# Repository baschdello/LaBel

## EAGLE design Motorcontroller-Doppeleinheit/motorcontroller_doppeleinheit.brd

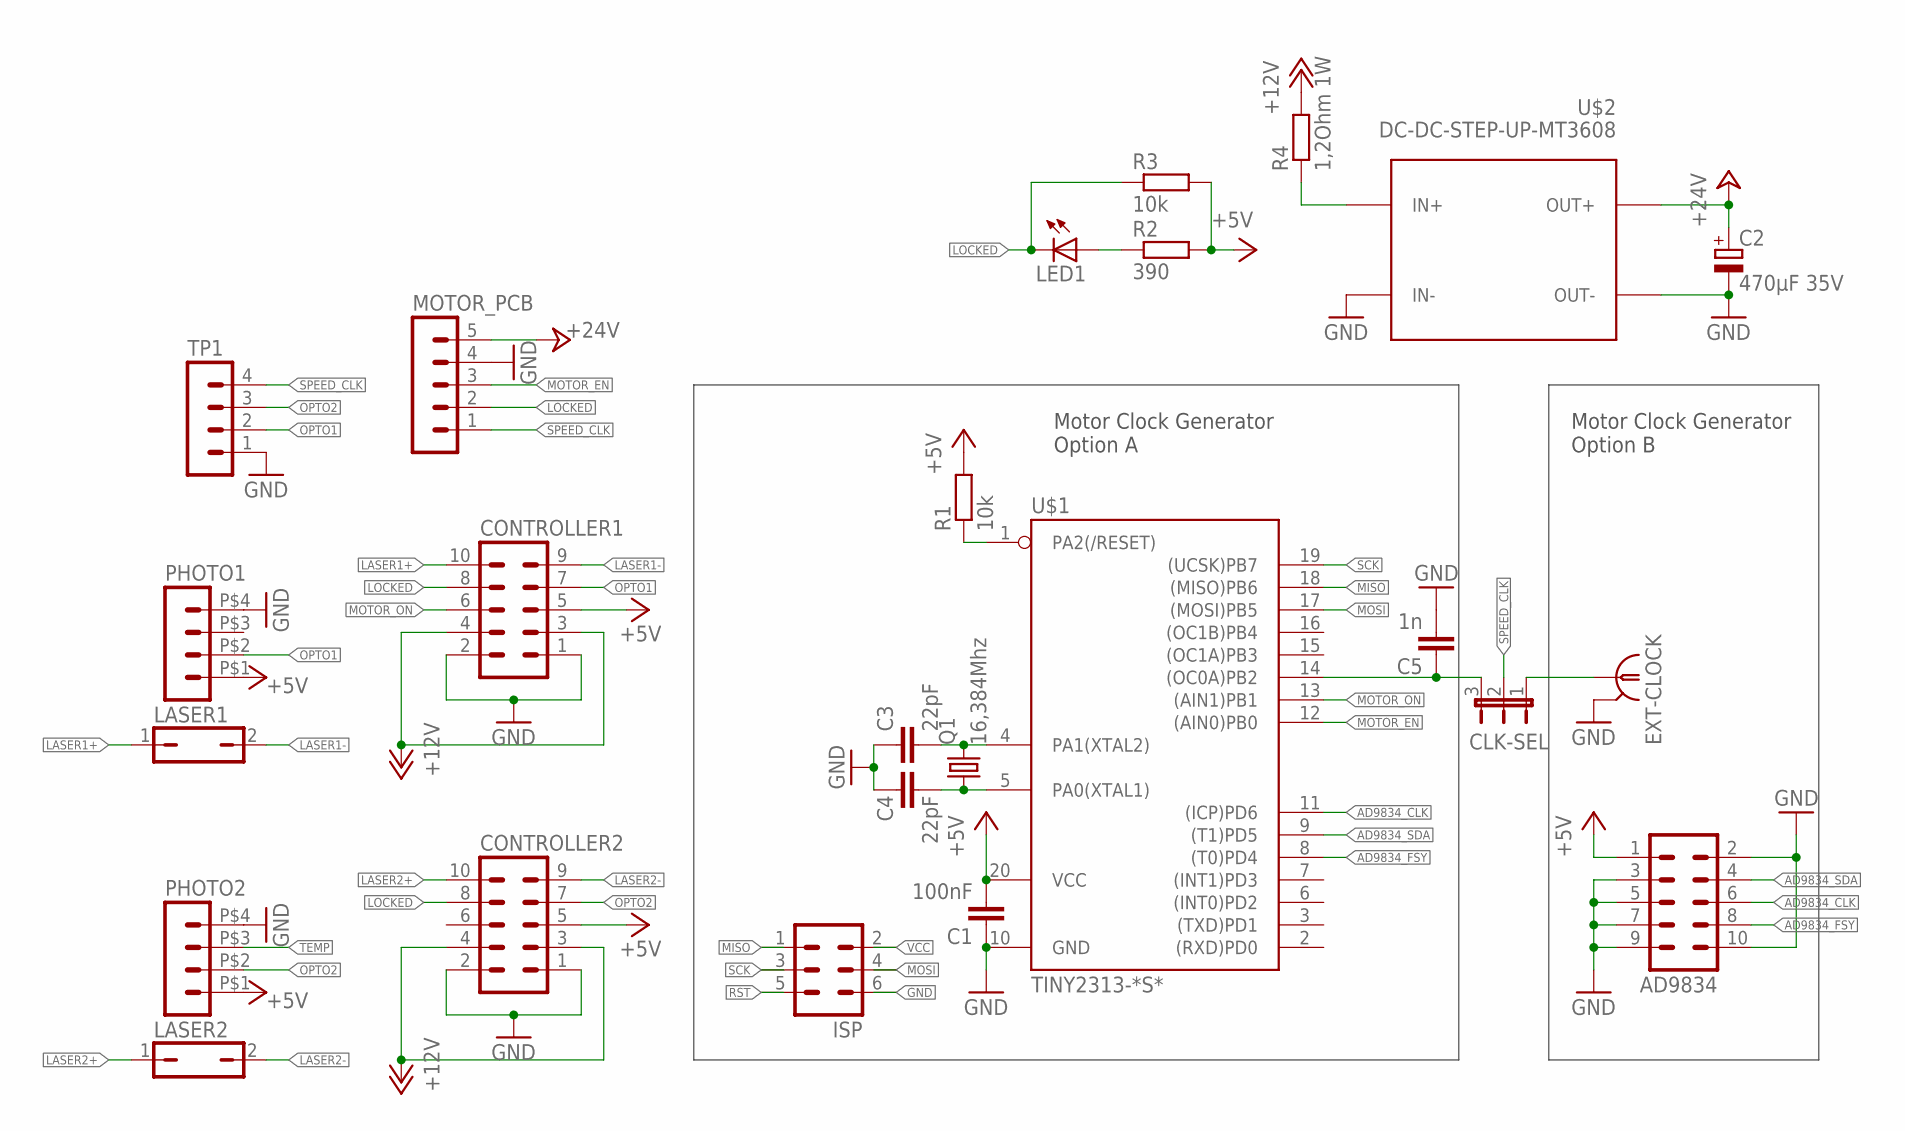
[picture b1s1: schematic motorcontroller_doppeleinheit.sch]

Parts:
AD9834: ML10
C1: 100nF; C1206
C2: 470µF 35V; E5-6
C3, C4: 22pF; C1206
C5: 1n; C1206
CLK-SEL: JP2E; JP2
CONTROLLER1, CONTROLLER2: ML10
EXT-CLOCK: LTI-SASF54GT
ISP: ML6L
LASER1, LASER2: JP1Q; JP1
LED1: LED3MM
MOTOR_PCB: MA05-1
PHOTO1, PHOTO2: FLAT_P4; FLAT_4P
Q1: 16,384Mhz; HC49UP
R1, R3: 10k; R1206
R2: 390; R1206
R4: 1,2Ohm 1W; 0411/15
TP1: MA04-1
U$1: TINY2313-*S*; SO20L$
U$2: DC-DC-STEP-UP-MT3608

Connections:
+5V: AD9834.1, C1.2, CONTROLLER1.5, CONTROLLER2.5, PHOTO1.P$1 (1), PHOTO2.P$1 (1), R1.2, R2.2, R3.2, U$1.20 (VCC)
+12V: CONTROLLER1.3, CONTROLLER1.4, CONTROLLER2.3, CONTROLLER2.4, R4.2
+24V: C2.+, MOTOR_PCB.5, U$2.OUT+
AD9834_CLK: AD9834.6, U$1.11 ((ICP)PD6)
AD9834_FSY: AD9834.8, U$1.8 ((T0)PD4)
AD9834_SDA: AD9834.4, U$1.9 ((T1)PD5)
GND: AD9834.2, AD9834.3, AD9834.5, AD9834.7, AD9834.9, AD9834.10, C1.1, C2.-, C3.1, C4.1, C5.2, CONTROLLER1.1, CONTROLLER1.2, CONTROLLER2.1, CONTROLLER2.2, EXT-CLOCK.2, EXT-CLOCK.3 (2), EXT-CLOCK.4 (2), EXT-CLOCK.5 (2), ISP.6, MOTOR_PCB.4, PHOTO1.P$4 (4), PHOTO2.P$4 (4), TP1.1, U$1.10 (GND), U$2.IN-, U$2.OUT-
LASER1+: CONTROLLER1.10, LASER1.1
LASER1-: CONTROLLER1.9, LASER1.2
LASER2+: CONTROLLER2.10, LASER2.1
LASER2-: CONTROLLER2.9, LASER2.2
LOCKED: CONTROLLER1.8, CONTROLLER2.8, LED1.K (C), MOTOR_PCB.2, R3.1
MISO: ISP.1, U$1.18 ((MISO)PB6)
MOSI: ISP.4, U$1.17 ((MOSI)PB5)
MOTOR_EN: MOTOR_PCB.3, U$1.12 ((AIN0)PB0)
MOTOR_ON: CONTROLLER1.6, U$1.13 ((AIN1)PB1)
unnamed: C4.2, Q1.1, U$1.5 (PA0(XTAL1))
unnamed: LED1.A, R2.1
unnamed: C5.1, CLK-SEL.3, U$1.14 ((OC0A)PB2)
unnamed: CLK-SEL.1, EXT-CLOCK.1
unnamed: C3.2, Q1.2, U$1.4 (PA1(XTAL2))
unnamed: R4.1, U$2.IN+
OPTO1: CONTROLLER1.7, PHOTO1.P$2 (2), TP1.2
OPTO2: CONTROLLER2.7, PHOTO2.P$2 (2), TP1.3
RST: ISP.5, R1.1, U$1.1 (PA2(/RESET))
SCK: ISP.3, U$1.19 ((UCSK)PB7)
SPEED_CLK: CLK-SEL.2, MOTOR_PCB.1, TP1.4
TEMP: PHOTO2.P$3 (3)
VCC: ISP.2

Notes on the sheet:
Motor Clock Generator Option A
Motor Clock Generator Option B

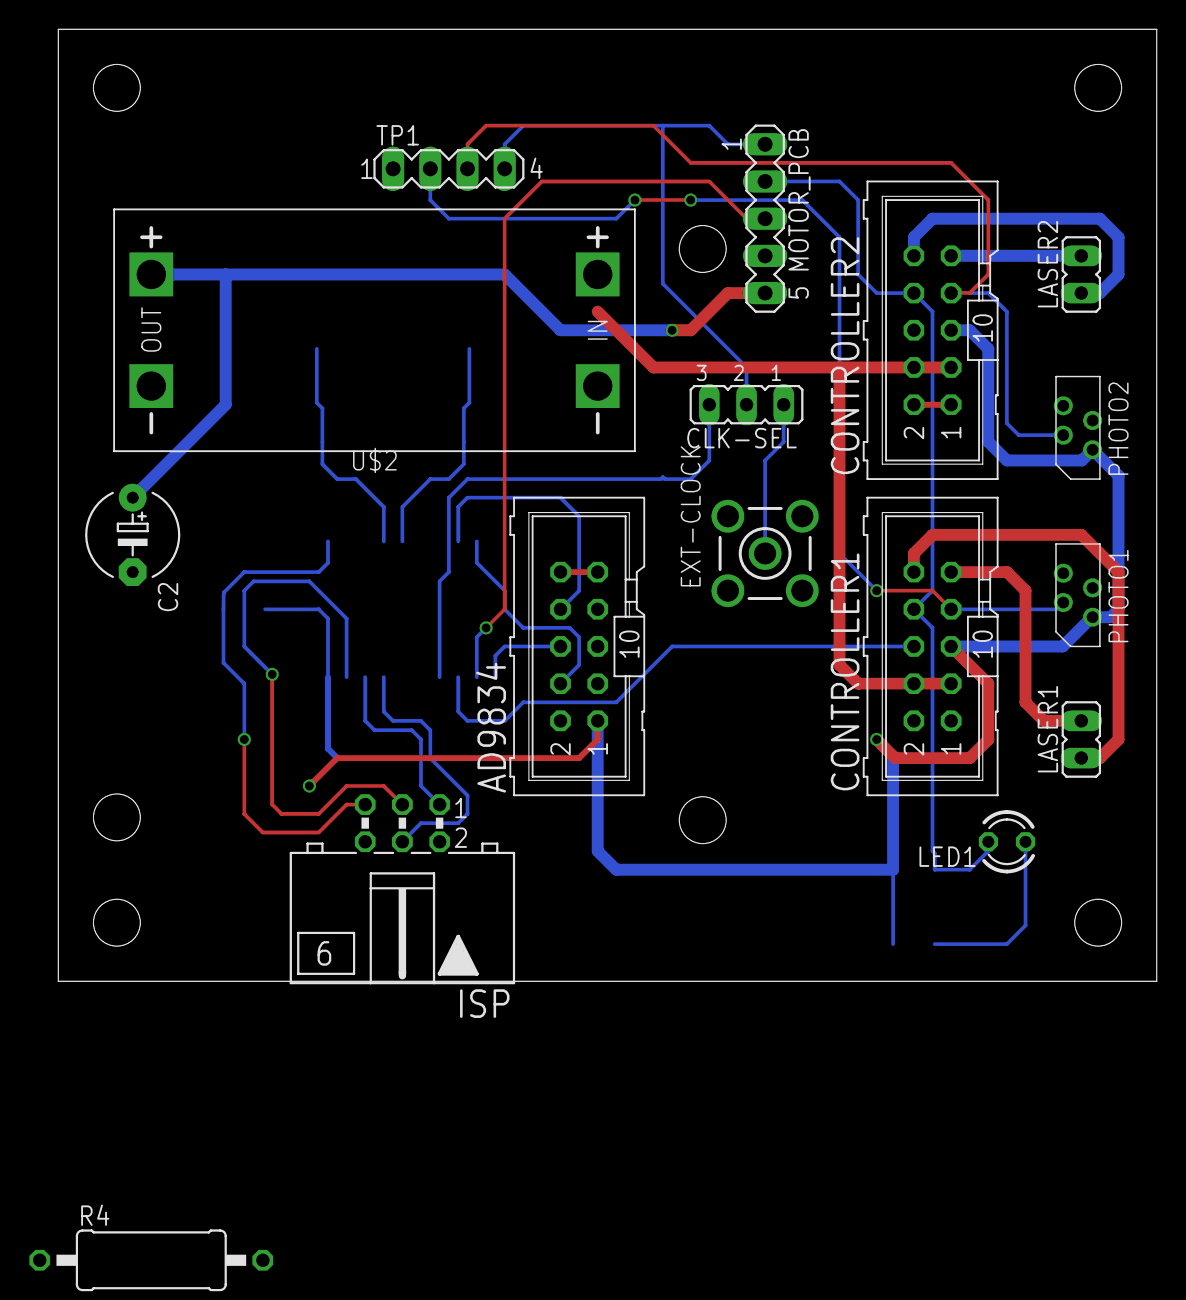
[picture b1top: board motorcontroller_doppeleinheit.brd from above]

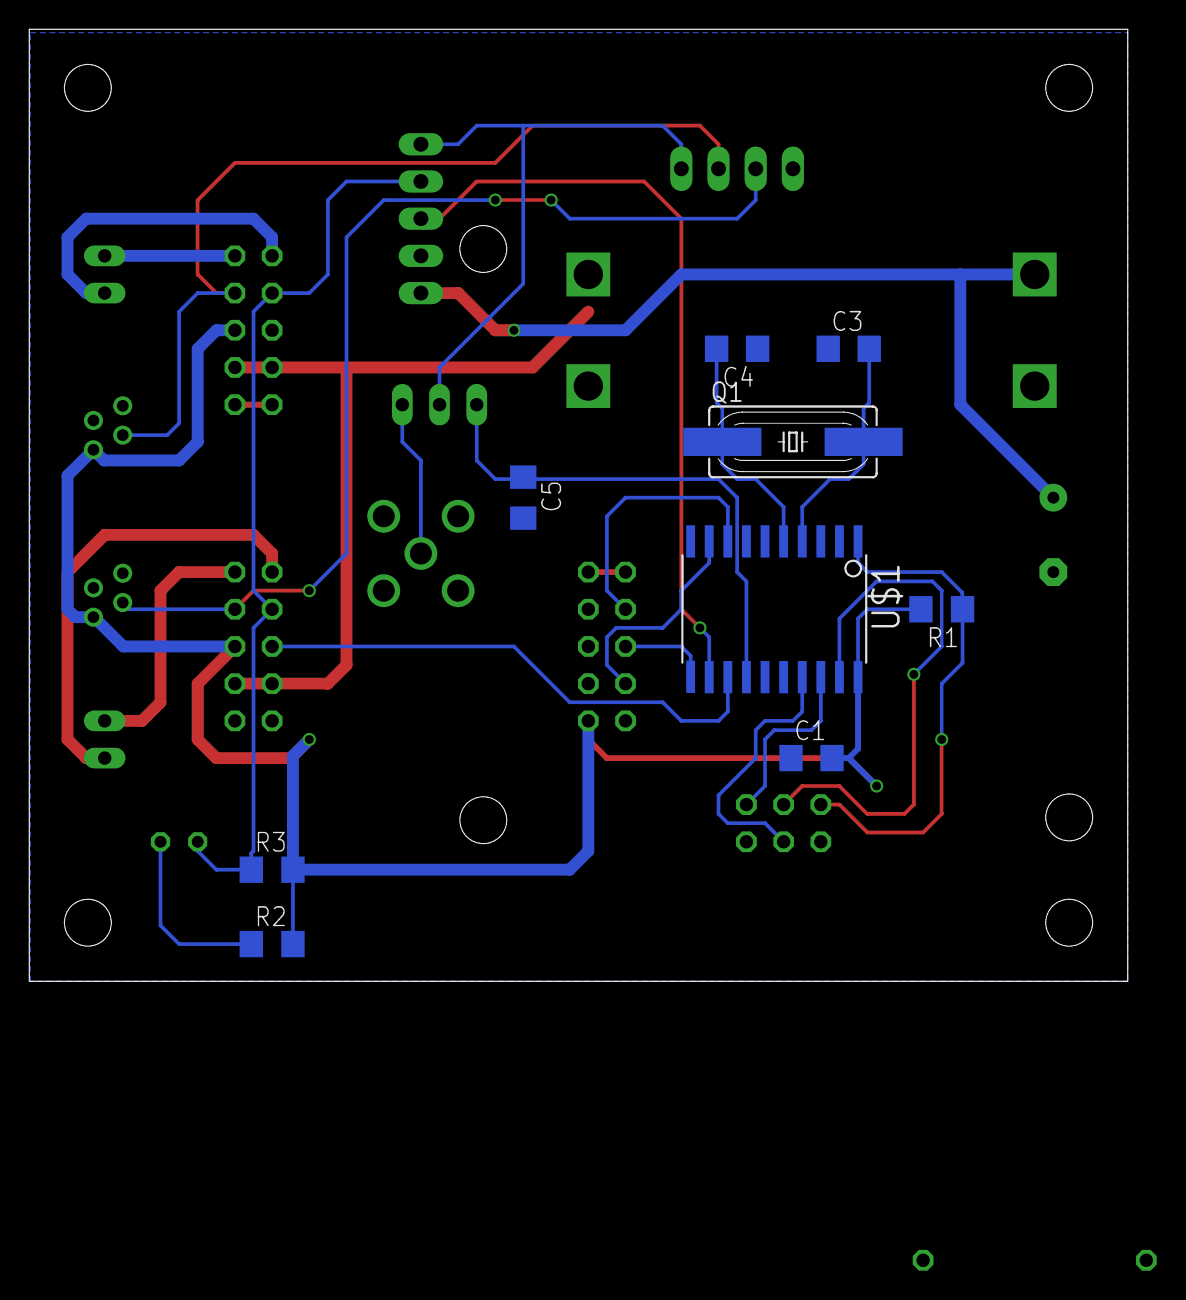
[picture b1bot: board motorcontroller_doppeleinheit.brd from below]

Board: 2 copper layers, 75.0 x 65.0 mm, 25 parts (9 on the bottom side), 27 nets.

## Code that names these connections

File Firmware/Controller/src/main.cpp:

#include <Arduino.h>

void setup() {
  // put your setup code here, to run once:
  DDRB   |=  (1 << PB0);														// MOTOR_EN für Polygon-Motor-Einheit
  DDRB   |=  (1 << PB2);														// PWM-Takt Ausgang
  DDRD   &= ~(1 << PB1);														// MOTOR_ON als Start-Anforderung von CONTROLLER1


  TCCR0A = (1 << COM0A0)|									// Set OC0B on Compare Match (OCR0B), clear on TOP (OCR0A)
    (1 << WGM00 ) | (1 << WGM01 ) ;									// Fast PWM mit OCR0A = TOP
  TCCR0B = (1 << WGM02 );

  OCR0A  = 0x2;																// TOP = 17 (zählt von 0 bis 17 = 18 Takte)
  OCR0B  = 0x00;																// Ab 0 wird das Ausgabe-Bit gesetzt

  TCCR0B |= (1<<CS02)|(1 << CS00);														// Takt = CLK/1 (kein Prescaler), start PWM
}

void loop() {
  // put your main code here, to run repeatedly:
  if( !(PINB & (1 << PB1)) )
  {
    //Polygon-Motor laufen lassen
    PORTB &= ~(1 << PB0);
  }
  else
  {
    //Polygon-Motor stoppen
    PORTB |= (1 << PB0);
  }
}

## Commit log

2020-03-01 added firmware for Tiny2313/4313
2020-03-02 Added C5, modified firmware because of inverted logic
2020-03-03 Added R4 for current limit if powering on

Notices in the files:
parts and their libraries:
diy-modules: Released under the Creative Commons Attribution 4.0 International License: http://creativecommons.org/licenses/by/4.0
